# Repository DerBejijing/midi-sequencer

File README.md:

# midi-sequencer
midi sequencer firmware for raspberry pico (moog 960-sequencer inspired)  
Inspired by moog, but turned out to look more like the MAQ16 lul  

## about  
This is a midi step sequencer inspired by the 960 made by moog in the 70s.
Since getting to know it, I have always loved the moog IIIp modular synthesizer, which is why I decided to build my own version of the sequencer complement B.
The cabinet holds two of those modules plus an additional "half-height" (actually about 60%) row, like the original one.
During the building process, I diverged from my original design over and over again, and in the end, I even had to borrow some parts from the other sequencer in the cabinet.  

## features  
- 3 rows with eight steps  
- rows can be played in parallel or serial  
- the lengths of all rows can be adjusted independently  
- a variable amount of ratcheting can be set per step  
- speed is adjustable  
- all values are sent over midi (channels 0-3 in parallel mode, 0 in serial)  

<br/>

TODO-List:  
---> add serial communication to controller  
---> find out how to make markdown add padding to a list next to an image >:(

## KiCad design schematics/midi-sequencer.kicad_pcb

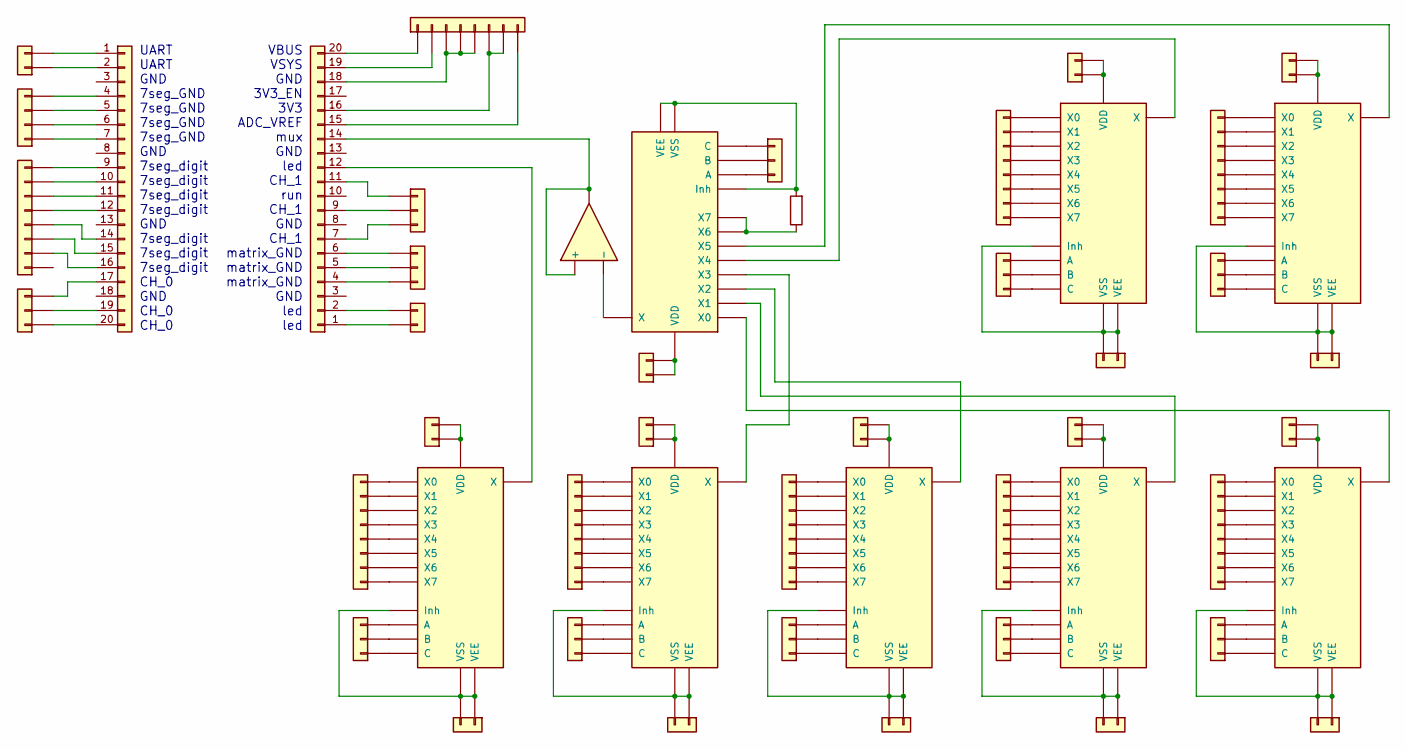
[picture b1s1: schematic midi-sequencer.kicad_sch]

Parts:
J1, J11, J12, J14, J17, J18, J19, J23, J24, J29, J30, J31, J32, J37, J38, J39, J40: Conn_01x02; PinHeader_1x02_P2.54mm_Vertical
J2: Conn_01x04; PinHeader_1x04_P2.54mm_Vertical
J3, J7, J13, J15, J21, J25, J27, J33, J35: Conn_01x08; PinHeader_1x08_P2.54mm_Vertical
J4, J8, J9, J10, J16, J20, J22, J26, J28, J34, J36: Conn_01x03; PinHeader_1x03_P2.54mm_Vertical
J5, J6: Conn_01x20; PinHeader_1x20_P2.54mm_Vertical
R1: R; R_Box_L13.0mm_W4.0mm_P9.00mm
U1, U3, U4, U5, U6, U7, U8, U9: 4051; DIP-16_W7.62mm_Socket
U2: OPA1622; DIP-14_W7.62mm_Socket

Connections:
unnamed: J1.1, J5.2
unnamed: J1.2, J5.1
unnamed: J2.1, J5.7
unnamed: J2.2, J5.6
unnamed: J2.3, J5.5
unnamed: J2.4, J5.4
unnamed: J3.2, J5.16
unnamed: J3.3, J5.15
unnamed: J3.4, J5.14
unnamed: J3.5, J5.12
unnamed: J3.6, J5.11
unnamed: J3.7, J5.10
unnamed: J3.8, J5.9
unnamed: J4.1, J5.20
unnamed: J4.2, J5.19
unnamed: J4.3, J5.17
unnamed: J6.7, J9.3
unnamed: J6.12, U1.3 (X)
unnamed: J7.1, U1.4 (X7)
unnamed: J7.2, U1.2 (X6)
unnamed: J7.3, U1.5 (X5)
unnamed: J7.4, U1.1 (X4)
unnamed: J7.5, U1.12 (X3)
unnamed: J7.6, U1.15 (X2)
unnamed: J7.7, U1.14 (X1)
unnamed: J7.8, U1.13 (X0)
unnamed: J8.1, U1.9 (C)
unnamed: J8.2, U1.10 (B)
unnamed: J8.3, U1.11 (A)
unnamed: J6.11, J9.1
unnamed: J6.9, J9.2
unnamed: J6.6, J10.1
unnamed: J6.5, J10.2
unnamed: J6.4, J10.3
unnamed: J6.2, J11.1
unnamed: J6.1, J11.2
unnamed: J12.1, J12.2, U1.16 (VDD)
unnamed: J6.20, J13.1
unnamed: J6.19, J13.2
unnamed: J6.18, J13.3, J13.4, J13.5
unnamed: J6.16, J13.6, J13.7
unnamed: J6.15, J13.8
unnamed: J14.1, J14.2, U1.6 (Inh), U1.7 (VEE), U1.8 (VSS)
unnamed: J15.1, U4.4 (X7)
unnamed: J15.2, U4.2 (X6)
unnamed: J15.3, U4.5 (X5)
unnamed: J15.4, U4.1 (X4)
unnamed: J15.5, U4.12 (X3)
unnamed: J15.6, U4.15 (X2)
unnamed: J15.7, U4.14 (X1)
unnamed: J15.8, U4.13 (X0)
unnamed: J16.1, U4.9 (C)
unnamed: J16.2, U4.10 (B)
unnamed: J16.3, U4.11 (A)
unnamed: J17.1, J17.2, U3.16 (VDD)
unnamed: J18.1, J18.2, U4.16 (VDD)
unnamed: J19.1, J19.2, U4.6 (Inh), U4.7 (VEE), U4.8 (VSS)
unnamed: J20.1, U3.9 (C)
unnamed: J20.2, U3.10 (B)
unnamed: J20.3, U3.11 (A)
unnamed: J21.1, U5.4 (X7)
unnamed: J21.2, U5.2 (X6)
unnamed: J21.3, U5.5 (X5)
unnamed: J21.4, U5.1 (X4)
unnamed: J21.5, U5.12 (X3)
unnamed: J21.6, U5.15 (X2)
unnamed: J21.7, U5.14 (X1)
unnamed: J21.8, U5.13 (X0)
unnamed: J22.1, U5.9 (C)
unnamed: J22.2, U5.10 (B)
unnamed: J22.3, U5.11 (A)
unnamed: J23.1, J23.2, U5.16 (VDD)
unnamed: J24.1, J24.2, U5.6 (Inh), U5.7 (VEE), U5.8 (VSS)
unnamed: J25.1, U6.4 (X7)
unnamed: J25.2, U6.2 (X6)
unnamed: J25.3, U6.5 (X5)
unnamed: J25.4, U6.1 (X4)
unnamed: J25.5, U6.12 (X3)
unnamed: J25.6, U6.15 (X2)
unnamed: J25.7, U6.14 (X1)
unnamed: J25.8, U6.13 (X0)
unnamed: J26.1, U6.9 (C)
unnamed: J26.2, U6.10 (B)
unnamed: J26.3, U6.11 (A)
unnamed: J27.1, U7.4 (X7)
unnamed: J27.2, U7.2 (X6)
unnamed: J27.3, U7.5 (X5)
unnamed: J27.4, U7.1 (X4)
unnamed: J27.5, U7.12 (X3)
unnamed: J27.6, U7.15 (X2)
unnamed: J27.7, U7.14 (X1)
unnamed: J27.8, U7.13 (X0)
unnamed: J28.1, U7.9 (C)
unnamed: J28.2, U7.10 (B)
unnamed: J28.3, U7.11 (A)
unnamed: J29.1, J29.2, U6.16 (VDD)
unnamed: J30.1, J30.2, U7.16 (VDD)
unnamed: J31.1, J31.2, U6.6 (Inh), U6.7 (VEE), U6.8 (VSS)
unnamed: J32.1, J32.2, U7.6 (Inh), U7.7 (VEE), U7.8 (VSS)
unnamed: J33.1, U8.4 (X7)
unnamed: J33.2, U8.2 (X6)
unnamed: J33.3, U8.5 (X5)
unnamed: J33.4, U8.1 (X4)
unnamed: J33.5, U8.12 (X3)
unnamed: J33.6, U8.15 (X2)
unnamed: J33.7, U8.14 (X1)
unnamed: J33.8, U8.13 (X0)
unnamed: J34.1, U8.9 (C)
unnamed: J34.2, U8.10 (B)
unnamed: J34.3, U8.11 (A)
unnamed: J35.1, U9.4 (X7)
unnamed: J35.2, U9.2 (X6)
unnamed: J35.3, U9.5 (X5)
unnamed: J35.4, U9.1 (X4)
unnamed: J35.5, U9.12 (X3)
unnamed: J35.6, U9.15 (X2)
unnamed: J35.7, U9.14 (X1)
unnamed: J35.8, U9.13 (X0)
unnamed: J36.1, U9.9 (C)
unnamed: J36.2, U9.10 (B)
unnamed: J36.3, U9.11 (A)
unnamed: J37.1, J37.2, U8.16 (VDD)
unnamed: J38.1, J38.2, U9.16 (VDD)
unnamed: J39.1, J39.2, U8.6 (Inh), U8.7 (VEE), U8.8 (VSS)
unnamed: J40.1, J40.2, U9.6 (Inh), U9.7 (VEE), U9.8 (VSS)
unnamed: R1.1, U3.2 (X6), U3.4 (X7)
unnamed 126: U2.4 (V-), U2.11 (V-); also elsewhere on the board
unnamed: U3.1 (X4), U6.3 (X)
unnamed: U3.5 (X5), U8.3 (X)
unnamed: U3.12 (X3), U4.3 (X)
unnamed: U3.13 (X0), U9.3 (X)
unnamed: U3.14 (X1), U7.3 (X)
unnamed: U3.15 (X2), U5.3 (X)

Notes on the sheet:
UART UART GND 7seg_GND 7seg_GND 7seg_GND 7seg_GND GND 7seg_digit 7seg_digit 7seg_digit 7seg_digit GND 7seg_digit 7seg_digit 7seg_digit CH_0 GND CH_0 CH_0
VBUS VSYS GND 3V3_EN 3V3 ADC_VREF mux GND led CH_1 run CH_1 GND CH_1 matrix_GND matrix_GND matrix_GND GND led led

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
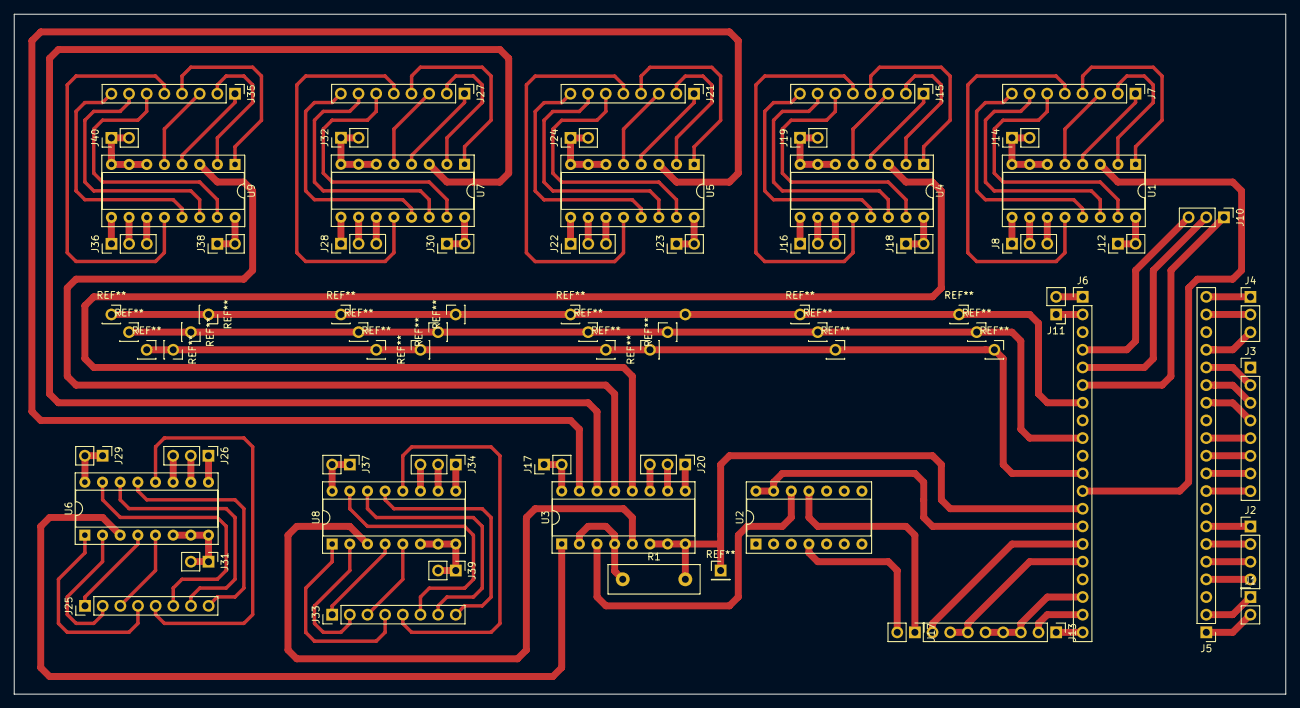
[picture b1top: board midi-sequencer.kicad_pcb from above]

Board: 2 copper layers, 182.9 x 97.8 mm, 50 parts (0 on the bottom side), 132 nets.

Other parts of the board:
J17#2: Conn_01x02; PinHeader_1x02_P2.54mm_Vertical

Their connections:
unnamed 126: J17#2.2; also elsewhere on the board

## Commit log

2023-01-07 somewhat working base
2023-01-07 add headers
2023-01-11 restructuring
2023-01-11 reading buttons
2023-01-11 interpolated reading and debouncing
2023-01-11 cleanup
2023-01-11 callbacks working
2023-01-11 remade callback system
2023-01-12 very evil function pointers to ? fixed
2023-01-12 fix sequencer tick function
2023-01-12 sequencer start/stop logic
2023-01-12 no longer skipping first stages
2023-01-12 update and apply changing values
2023-01-12 cleaning up and fixing some issues
2023-01-12 add bpm control
2023-01-12 cleaning up
2023-01-14 add seven segment display
2023-01-14 seven segment working
2023-01-14 seven segment refresh time
2023-01-14 fixed issues with seven segment display
2023-01-14 add indicator led support for serial/parallel mode
2023-01-15 add interface
2023-01-24 debugging stuff
2023-01-24 add serial mode
2023-01-24 sequencer serial operation
2023-01-24 ratcheting!
2023-01-24 ratcheting?
2023-01-26 ratcheting and interface
2023-01-26 update interface
2023-01-26 add schematics
2023-01-26 refactoring and commenting
2023-01-27 update sequencer
2023-01-27 update seven segment display
2023-01-29 fixed incorrect behavior in serial mode
2023-01-29 fixed timing issues
2023-01-29 add clear settings
2023-01-29 unless I redo the wiring...
2023-02-01 adding midi
2023-02-02 midi working
